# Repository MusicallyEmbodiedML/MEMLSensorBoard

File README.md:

# MEMLSensorBoard

Host board for up to 8 resistive sensors, with adjustable scale and offset.  Send to another board using serial or i2c.  Visual feedback with TFT screen.

## Hardware

Also hosts a ELI2040c board https://github.com/Emute-Lab-Instruments/ELI2040

## Software 

Runs on RP2040

Need TFT eSPI extension, with RP2040 GC9A01 driver

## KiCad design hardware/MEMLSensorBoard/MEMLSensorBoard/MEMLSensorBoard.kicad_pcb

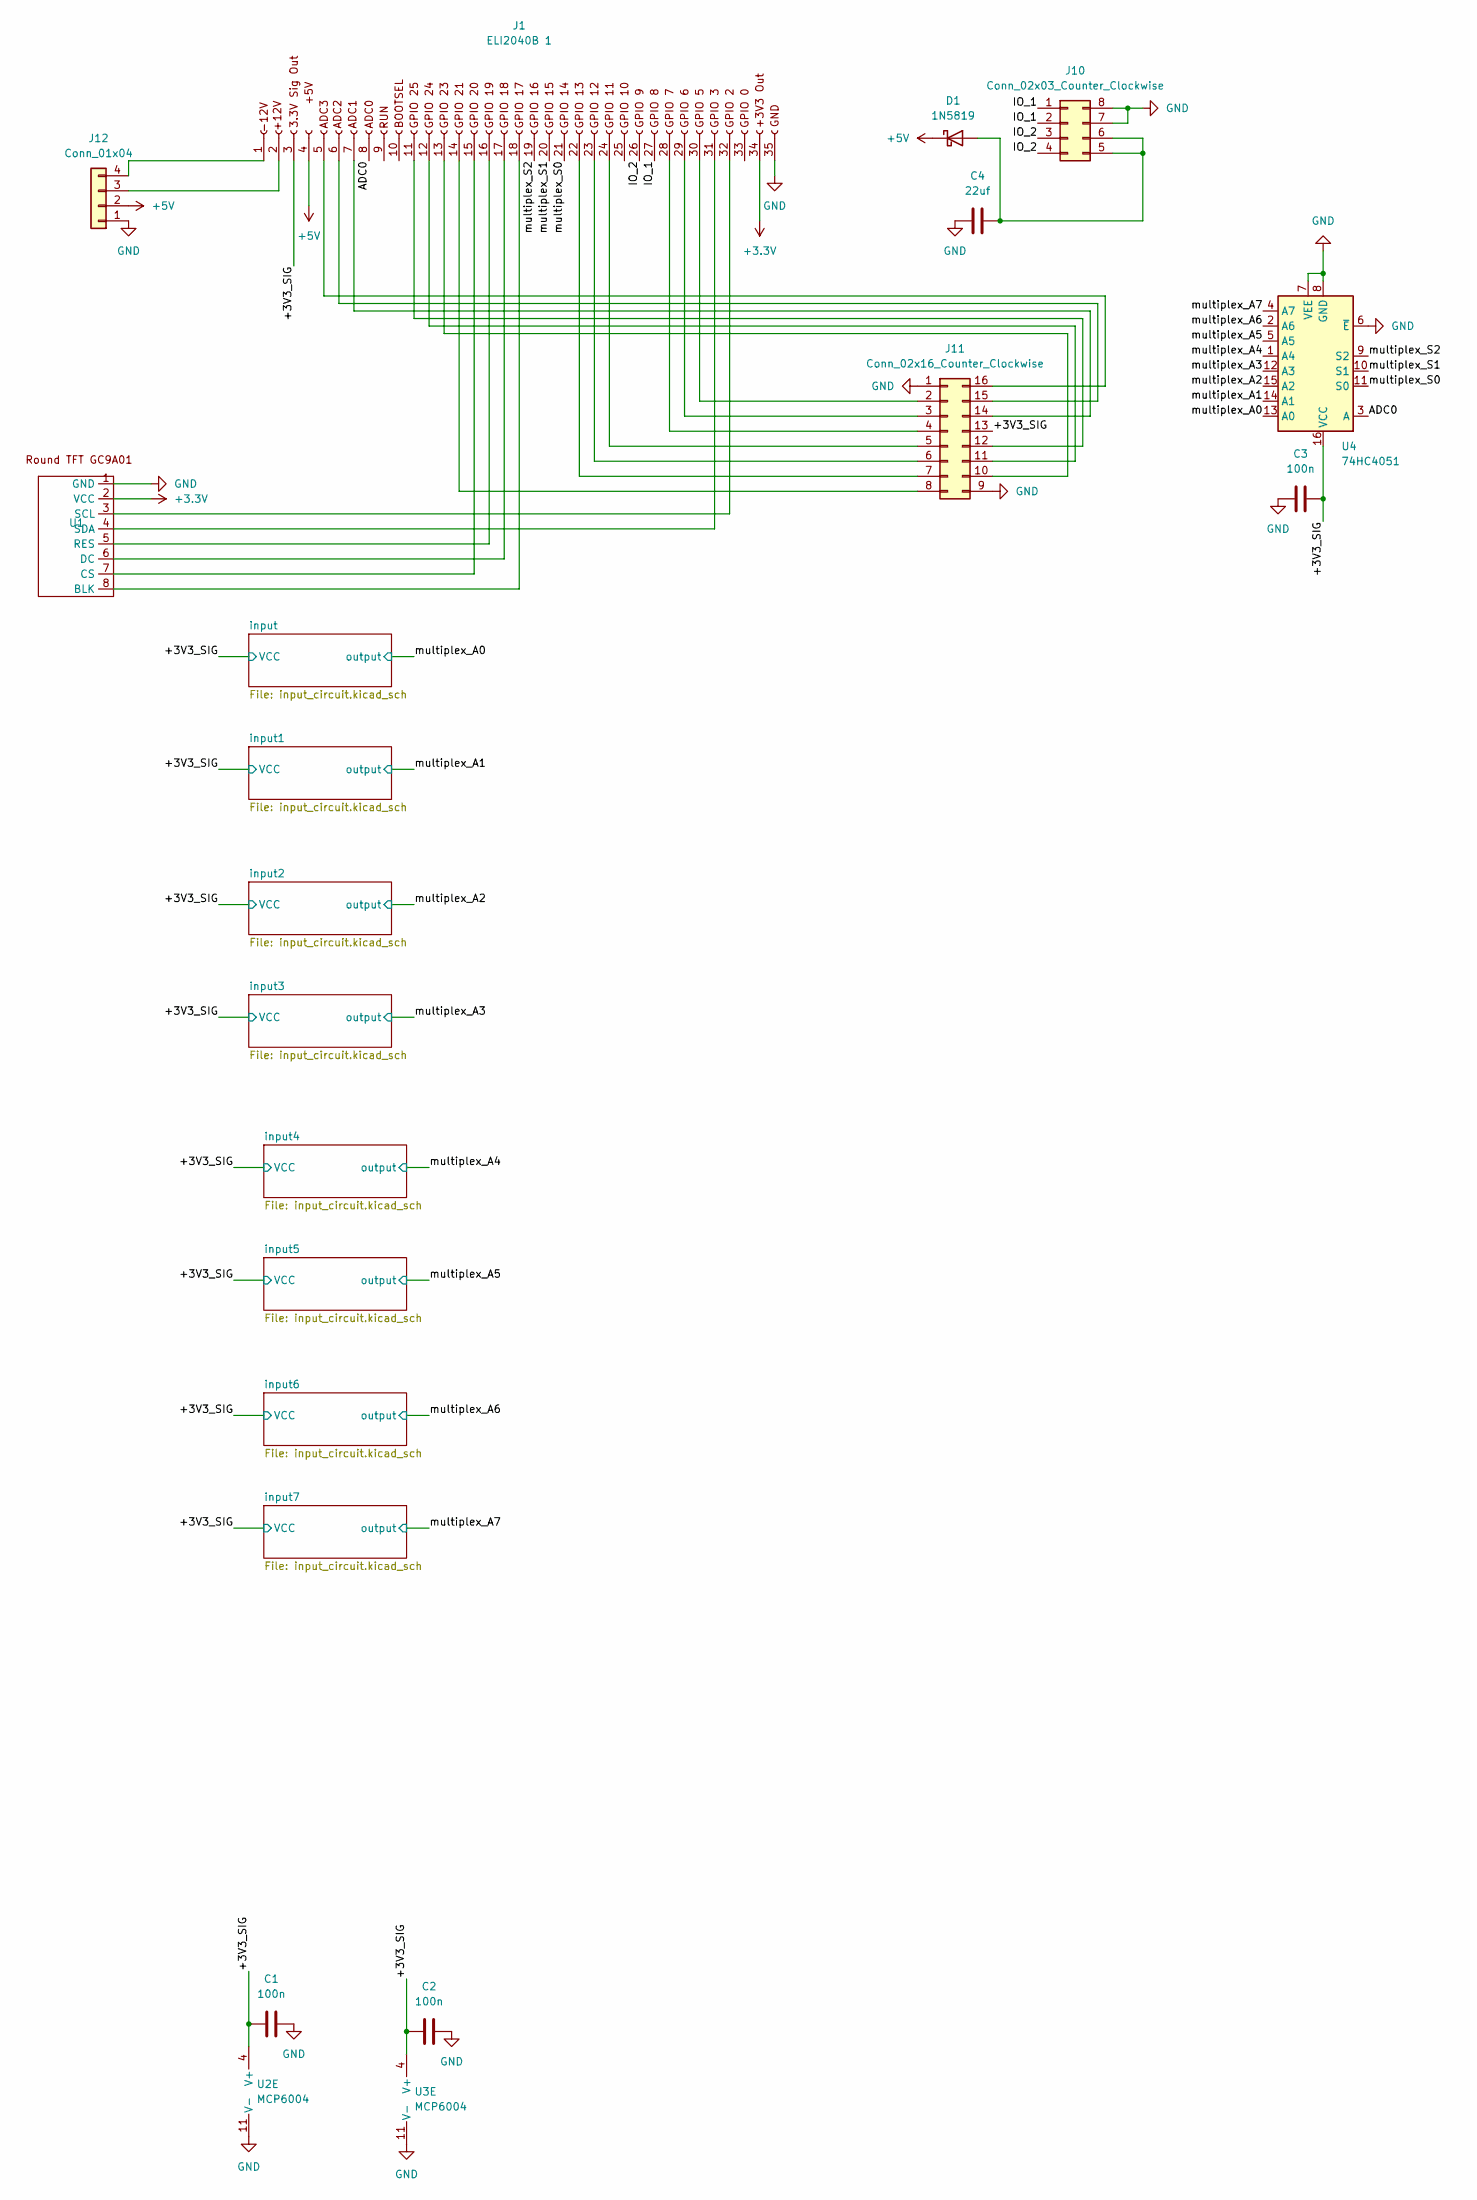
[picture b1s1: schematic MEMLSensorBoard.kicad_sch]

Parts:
C1, C2, C3: 100n; C_0603_1608Metric
C4: 22uf; C_0805_2012Metric
D1: 1N5819; D_SOD-323
J1: ELI2040B 1; PinSocket_1x35_P2.54mm_Vertical
J10: Conn_02x03_Counter_Clockwise; IDC-Header_2x04_P2.54mm_Vertical
J11: Conn_02x16_Counter_Clockwise; IDC-Header_2x08_P2.54mm_Vertical
J12: Conn_01x04; PinHeader_1x04_P2.54mm_Vertical
U1: Round TFT 240x240
U2, U3: MCP6004; TSSOP-14_4.4x5mm_P0.65mm
U4: 74HC4051; TSSOP-16_4.4x5mm_P0.65mm

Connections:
+3.3V: J1.34, U1.2 (VCC)
+5V: D1.1 (K), J1.4, J12.2
/+3V3_SIG: C1.1, C2.1, C3.1, J1.3, J11.13, U2.4 (V+), U3.4 (V+), U4.16 (VCC); also elsewhere on the board
/ADC0: J1.8, U4.3 (A)
/IO_1: J1.27, J10.1, J10.2
/IO_2: J1.26, J10.3, J10.4
/multiplex_A0: U2.1, U4.13 (A0); also elsewhere on the board
/multiplex_A1: U2.7, U4.14 (A1); also elsewhere on the board
/multiplex_A2: U4.15 (A2); also elsewhere on the board
/multiplex_A3: U2.14, U4.12 (A3); also elsewhere on the board
/multiplex_A4: U3.1, U4.1 (A4); also elsewhere on the board
/multiplex_A5: U3.7, U4.5 (A5); also elsewhere on the board
/multiplex_A6: U4.2 (A6); also elsewhere on the board
/multiplex_A7: U3.14, U4.4 (A7); also elsewhere on the board
/multiplex_S0: J1.21, U4.11 (S0)
/multiplex_S1: J1.20, U4.10 (S1)
/multiplex_S2: J1.19, U4.9 (S2)
GND: C1.2, C2.2, C3.2, C4.1, J1.35, J10.7, J10.8, J11.1, J11.9, J12.1, U1.1 (GND), U2.11 (V-), U3.11 (V-), U4.6 (~E), U4.7 (VEE), U4.8 (GND); also elsewhere on the board
unnamed: C4.2, D1.2 (A), J10.5, J10.6
unnamed: J1.2 (+12V), J12.3
unnamed: J1.1 (-12V), J12.4
unnamed: J1.5, J11.16
unnamed: J1.6, J11.15
unnamed: J1.7, J11.14
unnamed: J1.11, J11.12
unnamed: J1.12, J11.11
unnamed: J1.13, J11.10
unnamed: J1.14, J11.8
unnamed: J1.15, U1.7 (CS)
unnamed: J1.16, U1.5 (RES)
unnamed: J1.17, U1.6 (DC)
unnamed: J1.18, U1.8 (BLK)
unnamed: J1.22, J11.7
unnamed: J1.23, J11.6
unnamed: J1.24, J11.5
unnamed: J1.28, J11.4
unnamed: J1.29, J11.3
unnamed: J1.30, J11.2
unnamed: J1.31, U1.4 (SDA)
unnamed: J1.32, U1.3 (SCL)
unnamed 56: U2.3 (+); also elsewhere on the board
unnamed 57: U2.2 (-); also elsewhere on the board
unnamed 58: U2.5 (+); also elsewhere on the board
unnamed 59: U2.6 (-); also elsewhere on the board
unnamed 62: U2.12 (+); also elsewhere on the board
unnamed 63: U2.13 (-); also elsewhere on the board
unnamed 64: U3.3 (+); also elsewhere on the board
unnamed 65: U3.2 (-); also elsewhere on the board
unnamed 66: U3.5 (+); also elsewhere on the board
unnamed 67: U3.6 (-); also elsewhere on the board
unnamed 70: U3.12 (+); also elsewhere on the board
unnamed 71: U3.13 (-); also elsewhere on the board

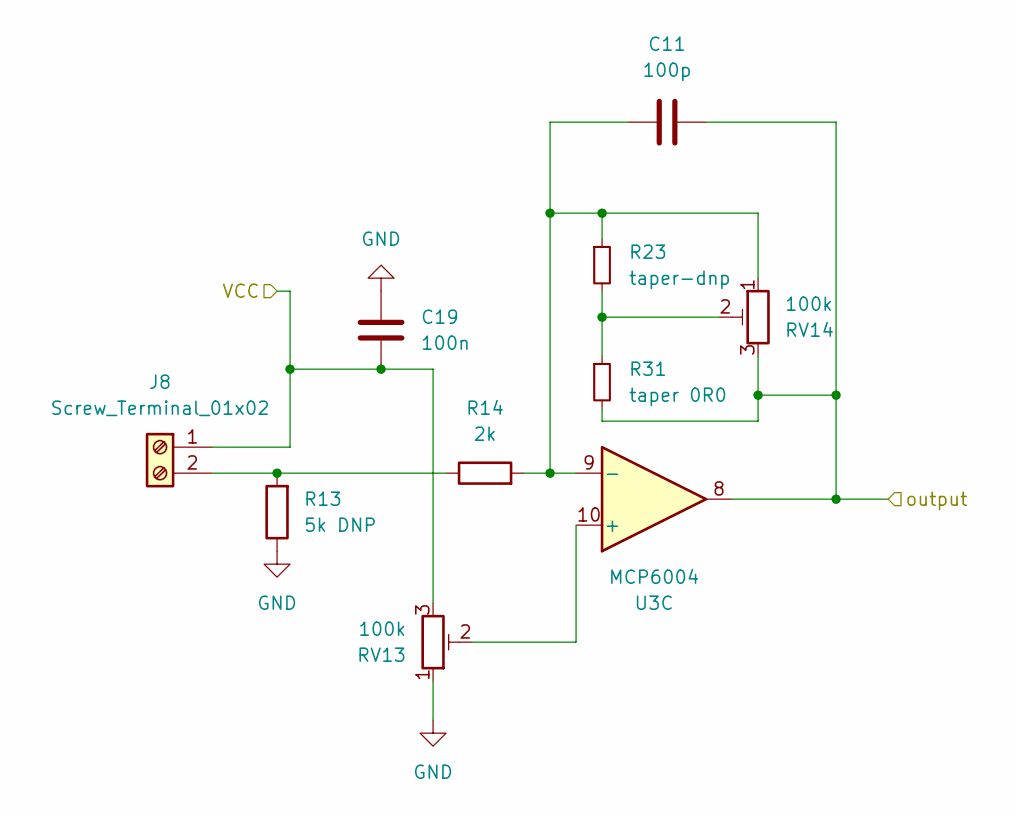
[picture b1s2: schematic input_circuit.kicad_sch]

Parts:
C11: 100p; C_Rect_L7.0mm_W2.5mm_P5.00mm; JLC C5359302
C19: 100n; C_0603_1608Metric
J8: Screw_Terminal_01x02; CONN-TH_WJ126V-5.0-2P; part WJ126V-5.0-2P; jlc C8404
R13: 5k DNP; R_Axial_DIN0207_L6.3mm_D2.5mm_P7.62mm_Horizontal
R14: 2k; R_0603_1608Metric
R23: taper-dnp; R_0603_1608Metric
R31: taper 0R0; R_0603_1608Metric; JLC C21189
RV13, RV14: 100k; TRIM_3306F-1-104
U3: MCP6004; TSSOP-14_4.4x5mm_P0.65mm

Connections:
/+3V3_SIG: C19.2, J8.1, RV13.3; also elsewhere on the board
/multiplex_A4: U3.1; also elsewhere on the board
/multiplex_A5: U3.7; also elsewhere on the board
/multiplex_A6: C11.2, R31.2, RV14.3, U3.8; also elsewhere on the board
/multiplex_A7: U3.14; also elsewhere on the board
GND: C19.1, R13.1, RV13.1; also elsewhere on the board
unnamed: J8.2, R13.2, R14.1
unnamed: R23.2, R31.1, RV14.2
unnamed 64: U3.3 (+); also elsewhere on the board
unnamed 65: U3.2 (-); also elsewhere on the board
unnamed 66: U3.5 (+); also elsewhere on the board
unnamed 67: U3.6 (-); also elsewhere on the board
unnamed: RV13.2, U3.10 (+)
unnamed: C11.1, R14.2, R23.1, RV14.1, U3.9 (-)
unnamed 70: U3.12 (+); also elsewhere on the board
unnamed 71: U3.13 (-); also elsewhere on the board

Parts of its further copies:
C5, C6, C7, C8, C9, C10, C12: 100p; C_Rect_L7.0mm_W2.5mm_P5.00mm; JLC C5359302
C13, C14, C15, C16, C17, C18, C20: 100n; C_0603_1608Metric
J2, J3, J4, J5, J6, J7, J9: Screw_Terminal_01x02; CONN-TH_WJ126V-5.0-2P; part WJ126V-5.0-2P; jlc C8404
R1, R3, R5, R7, R9, R11, R15: 5k DNP; R_Axial_DIN0207_L6.3mm_D2.5mm_P7.62mm_Horizontal
R2, R4, R6, R8, R10, R12, R16: 2k; R_0603_1608Metric
R17, R18, R19, R20, R21, R22, R24: taper-dnp; R_0603_1608Metric
R25, R26, R27, R28, R29, R30, R32: taper 0R0; R_0603_1608Metric; JLC C21189
RV1, RV2, RV3, RV4, RV5, RV6, RV7, RV8, RV9, RV10, RV11, RV12, RV15, RV16: 100k; TRIM_3306F-1-104

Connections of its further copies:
/+3V3_SIG: C13.2, C14.2, C15.2, C16.2, C17.2, C18.2, C20.2, J2.1, J3.1, J4.1, J5.1, J6.1, J7.1, J9.1, RV1.3, RV3.3, RV5.3, RV7.3, RV9.3, RV11.3, RV15.3; also elsewhere on the board
/multiplex_A0: C5.2, R25.2, RV2.3; also elsewhere on the board
/multiplex_A1: C6.2, R26.2, RV4.3; also elsewhere on the board
/multiplex_A2: C7.2, R27.2, RV6.3; also elsewhere on the board
/multiplex_A3: C8.2, R28.2, RV8.3; also elsewhere on the board
/multiplex_A4: C9.2, R29.2, RV10.3; also elsewhere on the board
/multiplex_A5: C10.2, R30.2, RV12.3; also elsewhere on the board
/multiplex_A7: C12.2, R32.2, RV16.3; also elsewhere on the board
GND: C13.1, C14.1, C15.1, C16.1, C17.1, C18.1, C20.1, R1.1, R3.1, R5.1, R7.1, R9.1, R11.1, R15.1, RV1.1, RV3.1, RV5.1, RV7.1, RV9.1, RV11.1, RV15.1; also elsewhere on the board
unnamed: J2.2, R1.2, R2.1
unnamed: J3.2, R3.2, R4.1
unnamed: J4.2, R5.2, R6.1
unnamed: J5.2, R7.2, R8.1
unnamed: J6.2, R9.2, R10.1
unnamed: J7.2, R11.2, R12.1
unnamed: J9.2, R15.2, R16.1
unnamed: R17.2, R25.1, RV2.2
unnamed: R18.2, R26.1, RV4.2
unnamed: R19.2, R27.1, RV6.2
unnamed: R20.2, R28.1, RV8.2
unnamed: R21.2, R29.1, RV10.2
unnamed: R22.2, R30.1, RV12.2
unnamed: R24.2, R32.1, RV16.2
unnamed 56: RV1.2; also elsewhere on the board
unnamed 57: C5.1, R2.2, R17.1, RV2.1; also elsewhere on the board
unnamed 58: RV3.2; also elsewhere on the board
unnamed 59: C6.1, R4.2, R18.1, RV4.1; also elsewhere on the board
unnamed 60: RV5.2; also elsewhere on the board
unnamed 61: C7.1, R6.2, R19.1, RV6.1; also elsewhere on the board
unnamed 62: RV7.2; also elsewhere on the board
unnamed 63: C8.1, R8.2, R20.1, RV8.1; also elsewhere on the board
unnamed 64: RV9.2; also elsewhere on the board
unnamed 65: C9.1, R10.2, R21.1, RV10.1; also elsewhere on the board
unnamed 66: RV11.2; also elsewhere on the board
unnamed 67: C10.1, R12.2, R22.1, RV12.1; also elsewhere on the board
unnamed 70: RV15.2; also elsewhere on the board
unnamed 71: C12.1, R16.2, R24.1, RV16.1; also elsewhere on the board

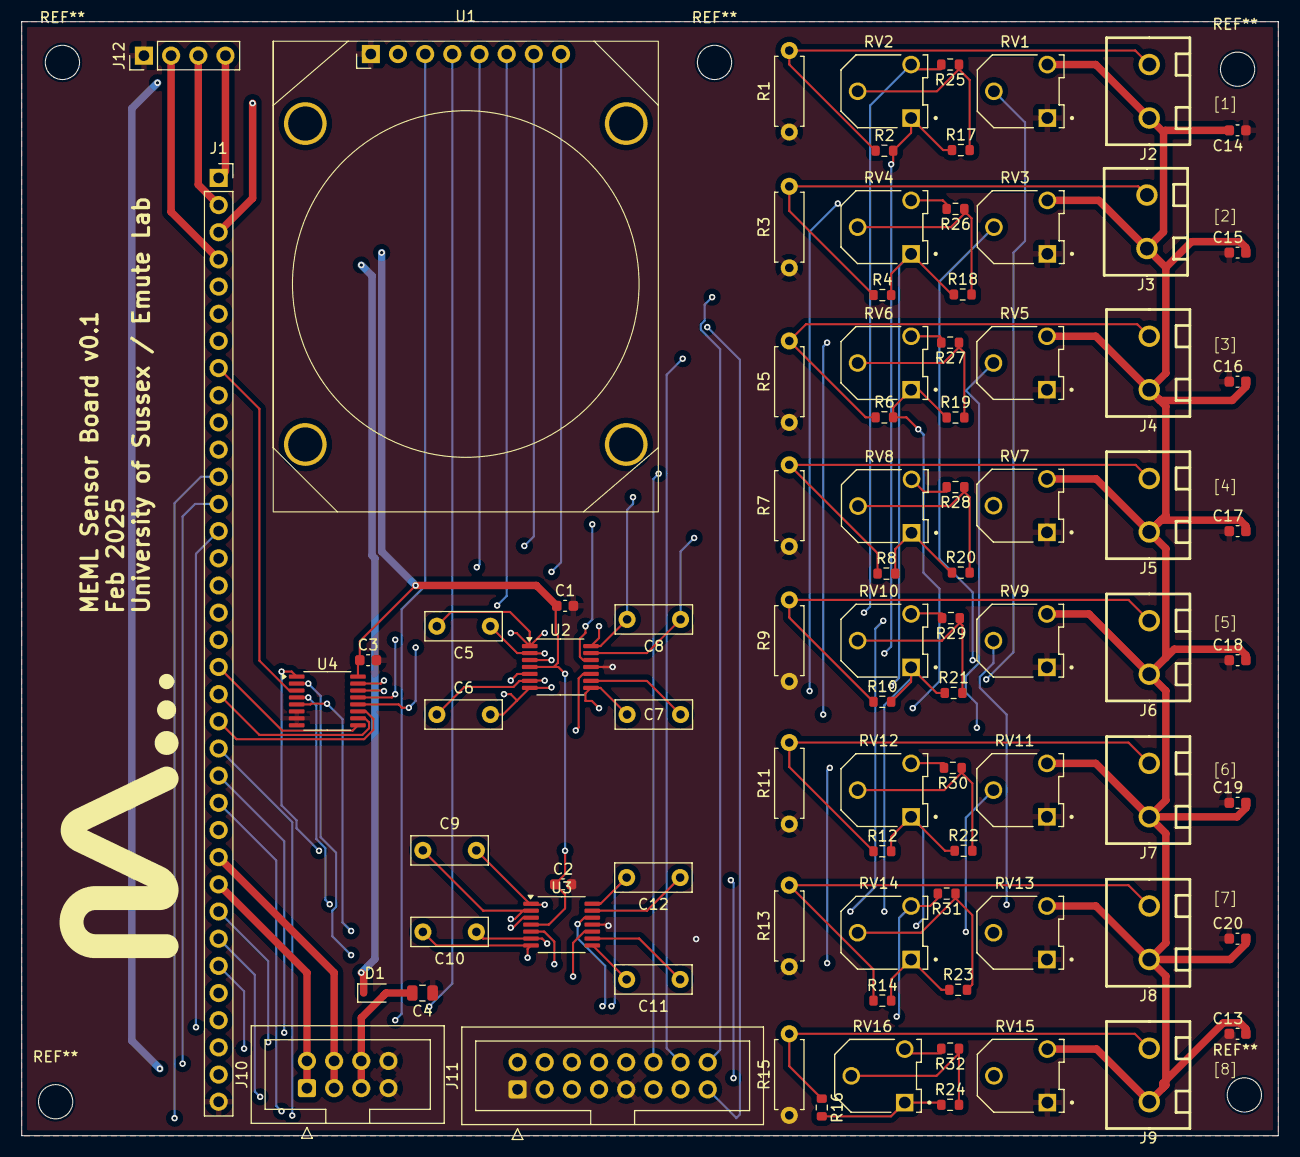
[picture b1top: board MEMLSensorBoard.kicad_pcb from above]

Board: 4 copper layers, 117.5 x 104.1 mm, 85 parts (0 on the bottom side), 72 nets.

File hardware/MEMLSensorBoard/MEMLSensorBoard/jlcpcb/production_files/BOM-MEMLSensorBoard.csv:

Comment,Designator,Footprint,LCSC
100n,"C1,C13,C14,C15,C16,C17,C18,C19,C2,C20,C3",C_0603_1608Metric,C14663
1N5819,D1,D_SOD-323,C191023
taper 0R0,"R25,R26,R27,R28,R29,R30,R31,R32",R_0603_1608Metric,C21189
2k,"R10,R12,R14,R16,R2,R4,R6,R8",R_0603_1608Metric,C22975
22uf,C4,C_0805_2012Metric,C45783
MCP6004,"U2,U3",TSSOP-14_4.4x5mm_P0.65mm,C50282
100p,"C10,C11,C12,C5,C6,C7,C8,C9",C_Rect_L7.0mm_W2.5mm_P5.00mm,C5359302
74HC4051,U4,TSSOP-16_4.4x5mm_P0.65mm,C5645
Screw_Terminal_01x02,"J2,J3,J4,J5,J6,J7,J8,J9",CONN-TH_WJ126V-5.0-2P,C8404
100k,RV11,TRIM_3306F-1-104,
100k,RV5,TRIM_3306F-1-104,
5k DNP,R3,R_Axial_DIN0207_L6.3mm_D2.5mm_P7.62mm_Horizontal,
~,U1,Round TFT 240x240,
100k,RV13,TRIM_3306F-1-104,
taper-dnp,R18,R_0603_1608Metric,
taper-dnp,R24,R_0603_1608Metric,
5k DNP,R7,R_Axial_DIN0207_L6.3mm_D2.5mm_P7.62mm_Horizontal,
100k,RV1,TRIM_3306F-1-104,
100k,RV12,TRIM_3306F-1-104,
ELI2040B 1,J1,PinSocket_1x35_P2.54mm_Vertical,
100k,RV8,TRIM_3306F-1-104,
5k DNP,R13,R_Axial_DIN0207_L6.3mm_D2.5mm_P7.62mm_Horizontal,
taper-dnp,R19,R_0603_1608Metric,
5k DNP,R9,R_Axial_DIN0207_L6.3mm_D2.5mm_P7.62mm_Horizontal,
Conn_02x03_Counter_Clockwise,J10,IDC-Header_2x04_P2.54mm_Vertical,
100k,RV9,TRIM_3306F-1-104,
100k,RV7,TRIM_3306F-1-104,
100k,RV3,TRIM_3306F-1-104,
100k,RV6,TRIM_3306F-1-104,
5k DNP,R1,R_Axial_DIN0207_L6.3mm_D2.5mm_P7.62mm_Horizontal,
100k,RV10,TRIM_3306F-1-104,
100k,RV4,TRIM_3306F-1-104,
100k,RV16,TRIM_3306F-1-104,
taper-dnp,R20,R_0603_1608Metric,
100k,RV14,TRIM_3306F-1-104,
5k DNP,R11,R_Axial_DIN0207_L6.3mm_D2.5mm_P7.62mm_Horizontal,
Conn_01x04,J12,PinHeader_1x04_P2.54mm_Vertical,
100k,RV15,TRIM_3306F-1-104,
taper-dnp,R21,R_0603_1608Metric,
5k DNP,R15,R_Axial_DIN0207_L6.3mm_D2.5mm_P7.62mm_Horizontal,
Conn_02x16_Counter_Clockwise,J11,IDC-Header_2x08_P2.54mm_Vertical,
5k DNP,R5,R_Axial_DIN0207_L6.3mm_D2.5mm_P7.62mm_Horizontal,
taper-dnp,R22,R_0603_1608Metric,
100k,RV2,TRIM_3306F-1-104,
taper-dnp,R17,R_0603_1608Metric,
taper-dnp,R23,R_0603_1608Metric,

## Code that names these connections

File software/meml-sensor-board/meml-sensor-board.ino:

#include <TFT_eSPI.h>
#include <array>
#include "pico/util/queue.h"
#include "SerialComms.hpp"

#define FAST_MEM __not_in_flash("data")

constexpr size_t MULTIPLEX_S0 = 14;
constexpr size_t MULTIPLEX_S1 = 15;
constexpr size_t MULTIPLEX_S2 = 16;


TFT_eSPI tft = TFT_eSPI();  // Invoke custom library
struct repeating_timer timerDisplay;

//sensors
std::array<size_t, 8> FAST_MEM sensorReadings, sensorReadingsCore1;
static queue_t FAST_MEM q_sensors;


inline bool __not_in_flash_func(displayUpdate)(__unused struct repeating_timer *t) {
  constexpr int barwidth = 16;
  constexpr int barheight=135;
  constexpr int barbase= 120 - (barheight/2.0);
  constexpr int barGap=18;
  constexpr int barcol = TFT_RED;
  constexpr int barcol2 = TFT_BLUE;
  constexpr int barLeft = 120 - (barGap*4);
  if (queue_try_remove(&q_sensors, sensorReadingsCore1.data())) {
    for(size_t i=0; i < 8; i++) {
      int thisBarHeight = barheight * (sensorReadingsCore1[i] / 4096.0);
      thisBarHeight = max(5, thisBarHeight);
      thisBarHeight = min(barheight, thisBarHeight);
      Serial.printf("%d %d %d\n", i, thisBarHeight, barheight - thisBarHeight);
      tft.fillRect(barLeft + (i * barGap), barbase, barwidth, barbase + thisBarHeight, barcol);
      tft.fillRect(barLeft + (i * barGap), barbase + thisBarHeight, barwidth, barheight - thisBarHeight, barcol2);
    }
  }
  return true;
}


void setup() {
  // put your setup code here, to run once:
  pinMode(22,1);
  pinMode(MULTIPLEX_S0, 1);
  pinMode(MULTIPLEX_S1, 1);
  pinMode(MULTIPLEX_S2, 1);
  digitalWrite(22,1);
  analogReadResolution(11);

  
  queue_init(&q_sensors, sizeof(float)*sensorReadings.size(), 1);

  for(auto &v: sensorReadings) {
    v=0;
  }
  Serial.begin();
  Serial2.setRX(9);
  Serial2.setTX(8);  
  Serial2.begin(115200);

  tft.begin();
  tft.setRotation(1);
  tft.setFreeFont(&FreeSans18pt7b);
  tft.fillScreen(TFT_GREEN);



}



void loop() {

  for(size_t sensorIdx=0; sensorIdx < 8; sensorIdx++) {
    
    //set the input using the multiplexer data lines
    digitalWrite(MULTIPLEX_S0, sensorIdx & 0b1);
    digitalWrite(MULTIPLEX_S1, (sensorIdx>>1) & 0b1);
    digitalWrite(MULTIPLEX_S2, (sensorIdx>>2) & 0b1);
    //;let the multiplexer settle
    delayMicroseconds(50);

    //make a reading
    auto ain = analogRead(26);
    sensorReadings[sensorIdx] = ain;
    queue_try_add(&q_sensors, sensorReadings.data());
    sendOverSerial(sensorIdx, ain / 2047.0);
    delay(1);
  }
  delay(30);
}

void setup1() {
  add_repeating_timer_ms(-39, displayUpdate, NULL, &timerDisplay);
}

void loop1() {
}

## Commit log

2025-06-21 latest
